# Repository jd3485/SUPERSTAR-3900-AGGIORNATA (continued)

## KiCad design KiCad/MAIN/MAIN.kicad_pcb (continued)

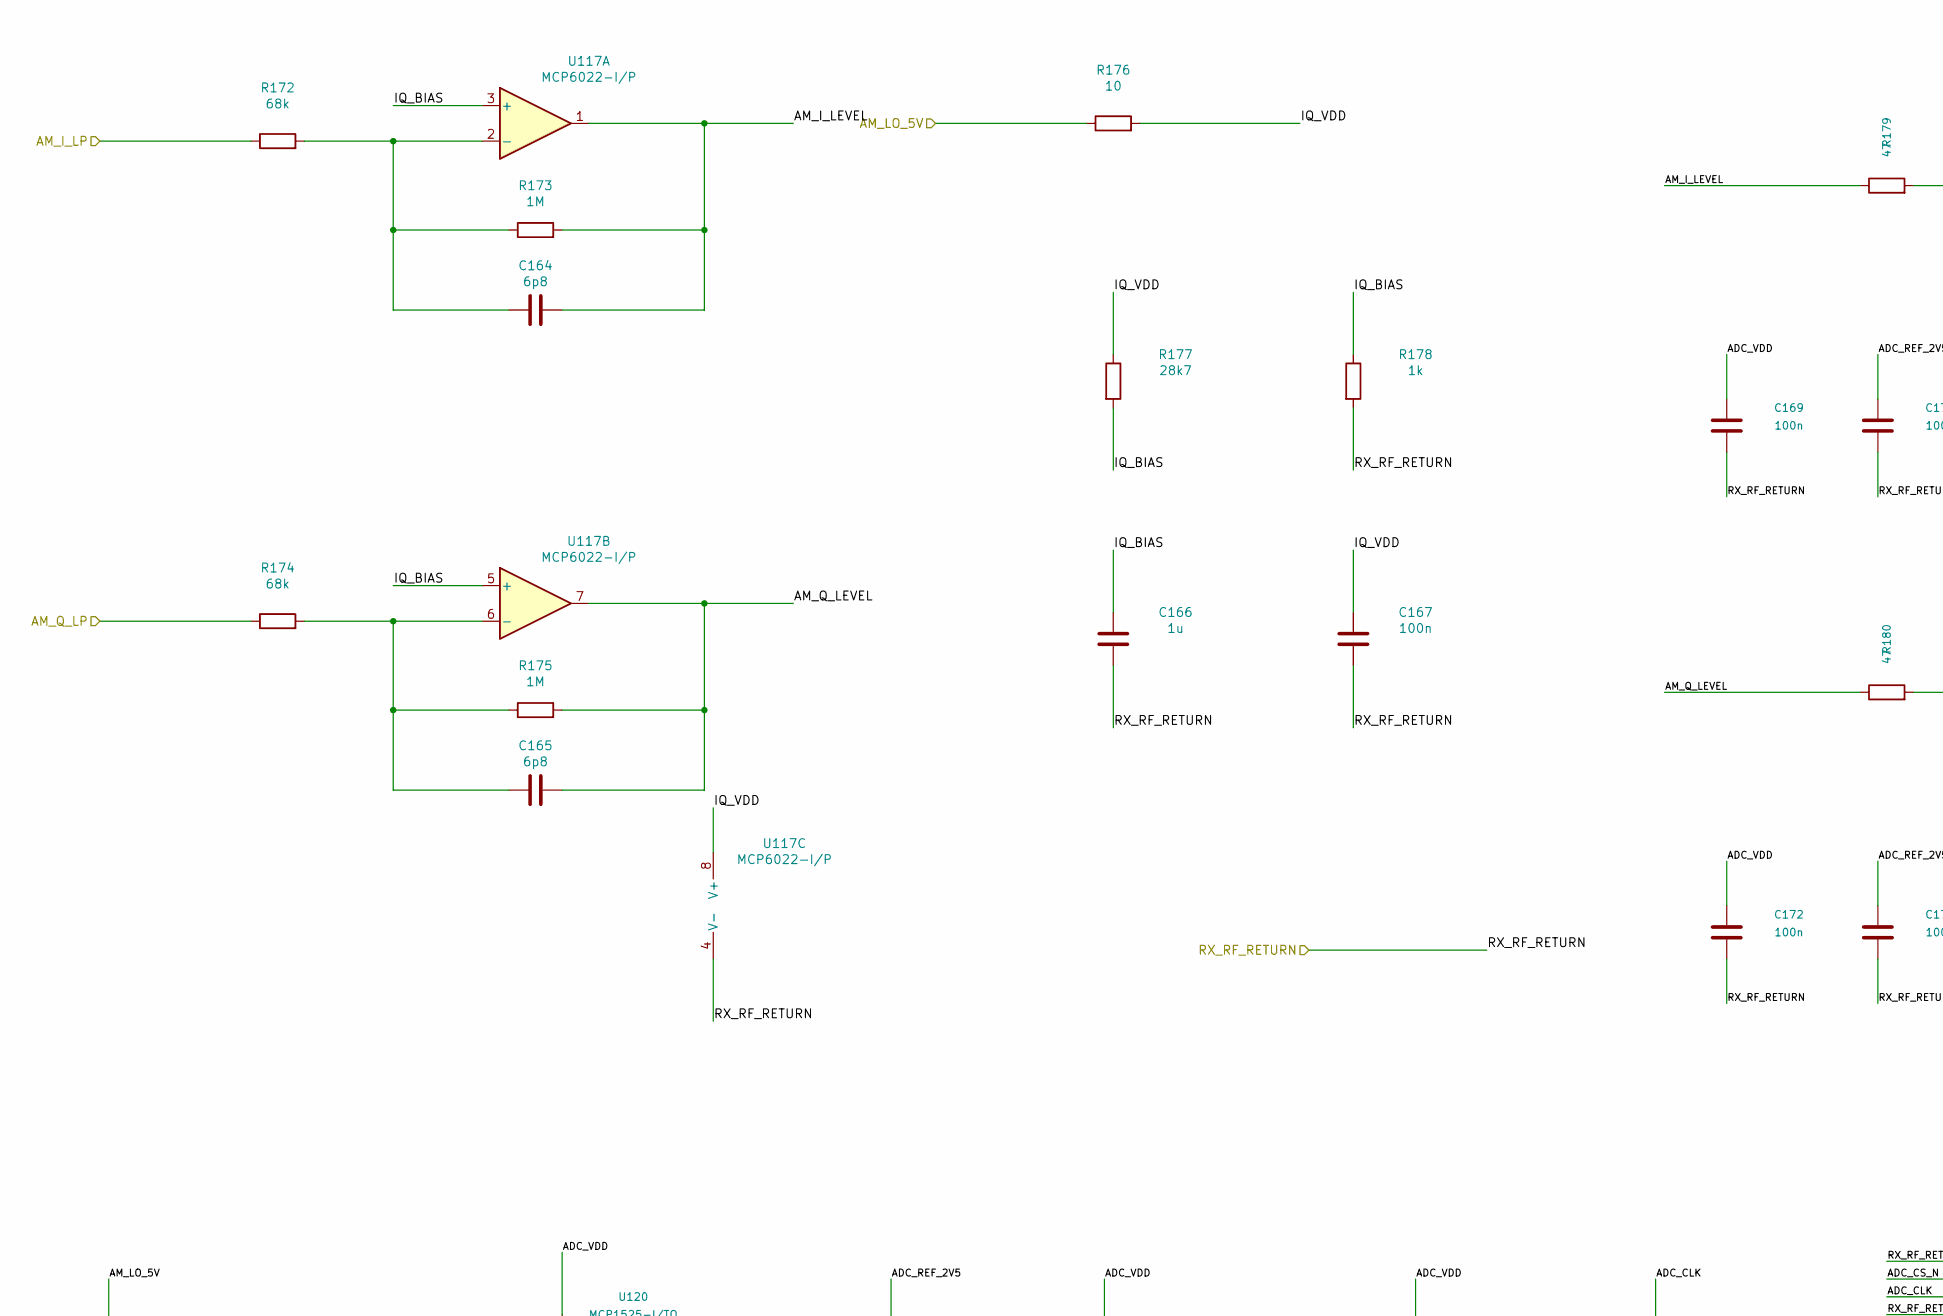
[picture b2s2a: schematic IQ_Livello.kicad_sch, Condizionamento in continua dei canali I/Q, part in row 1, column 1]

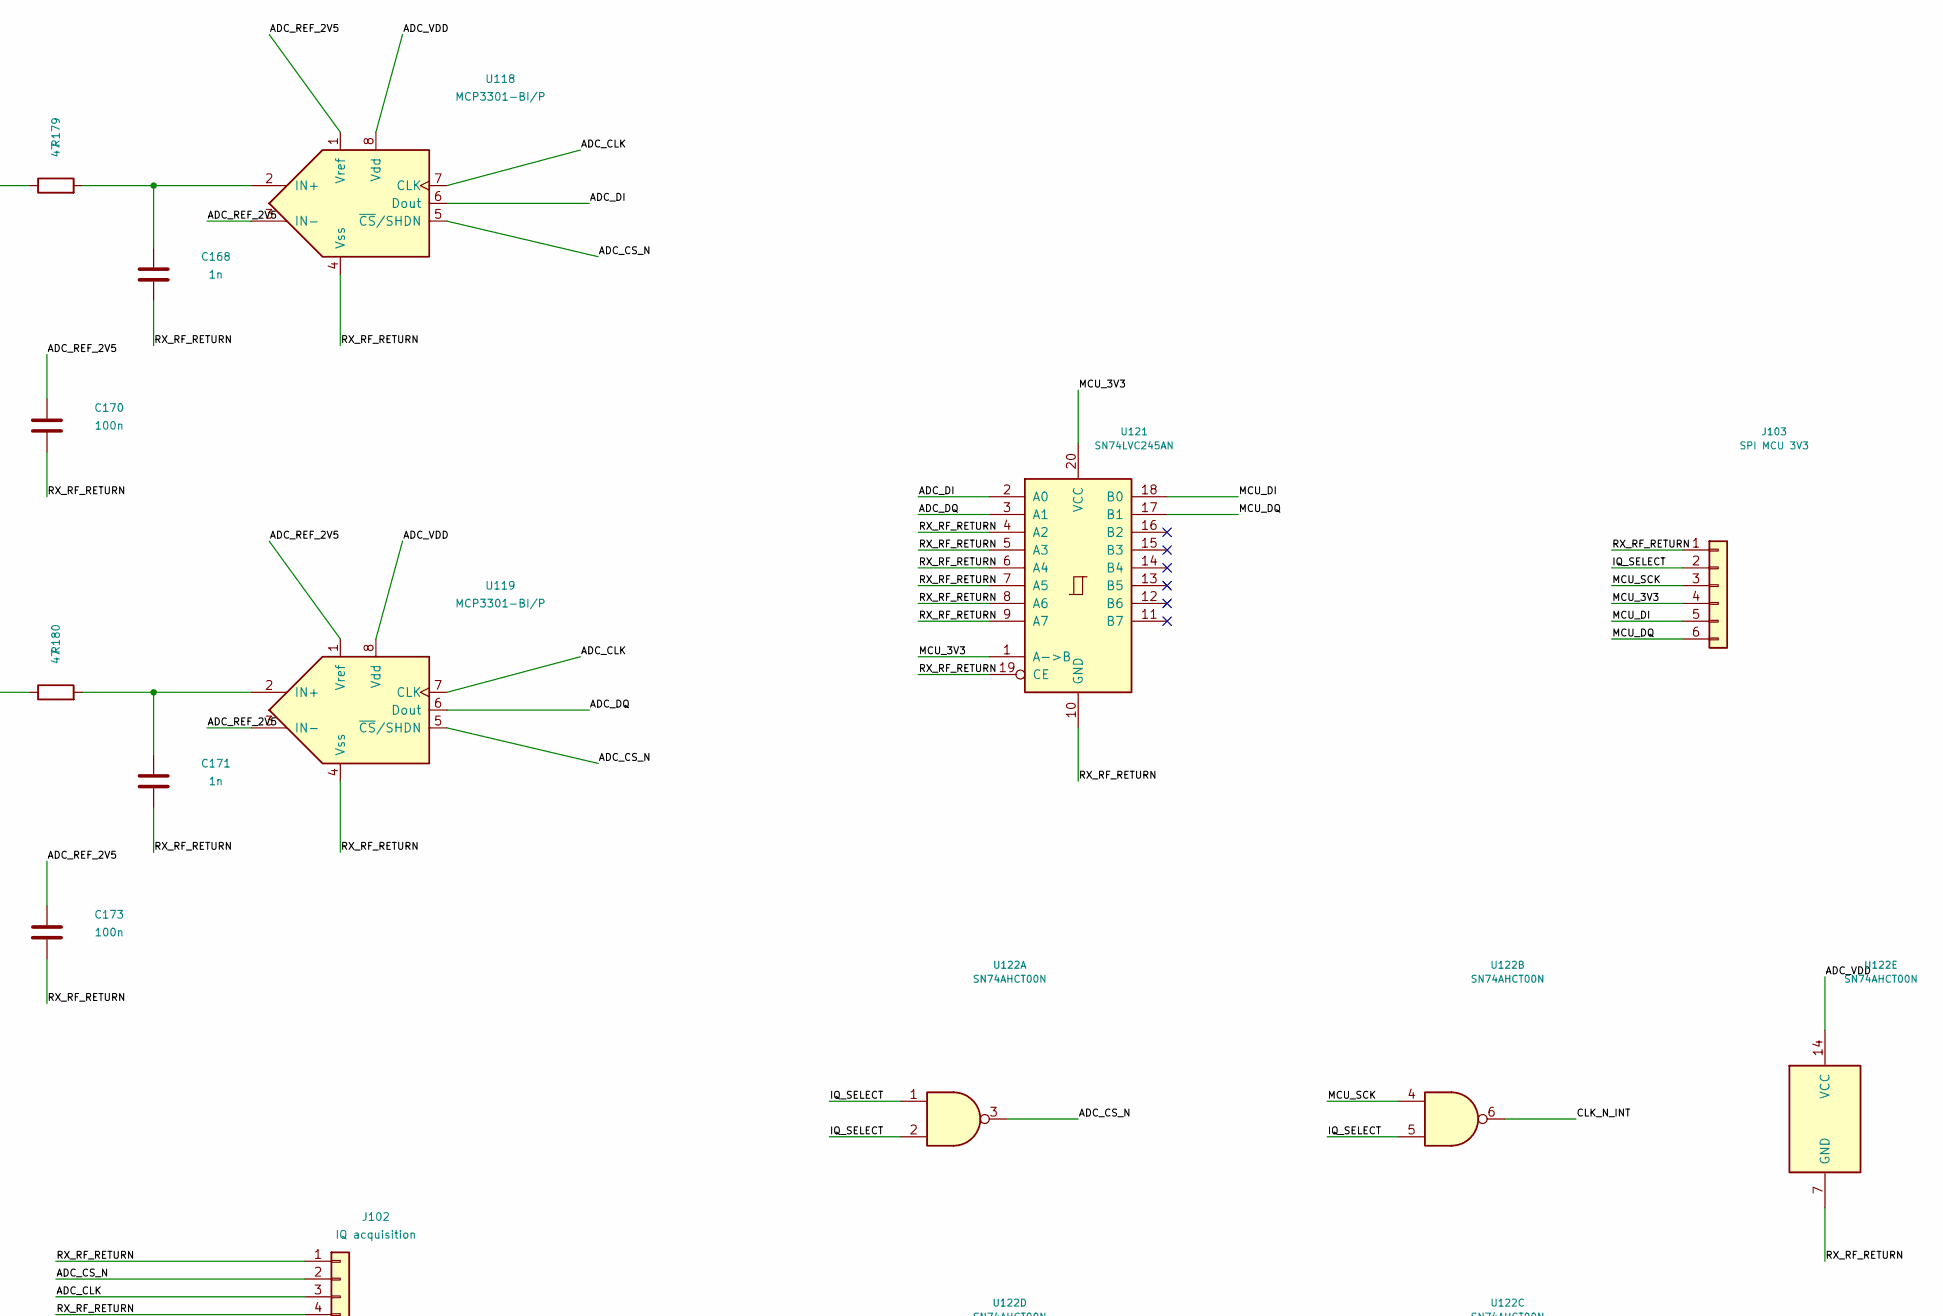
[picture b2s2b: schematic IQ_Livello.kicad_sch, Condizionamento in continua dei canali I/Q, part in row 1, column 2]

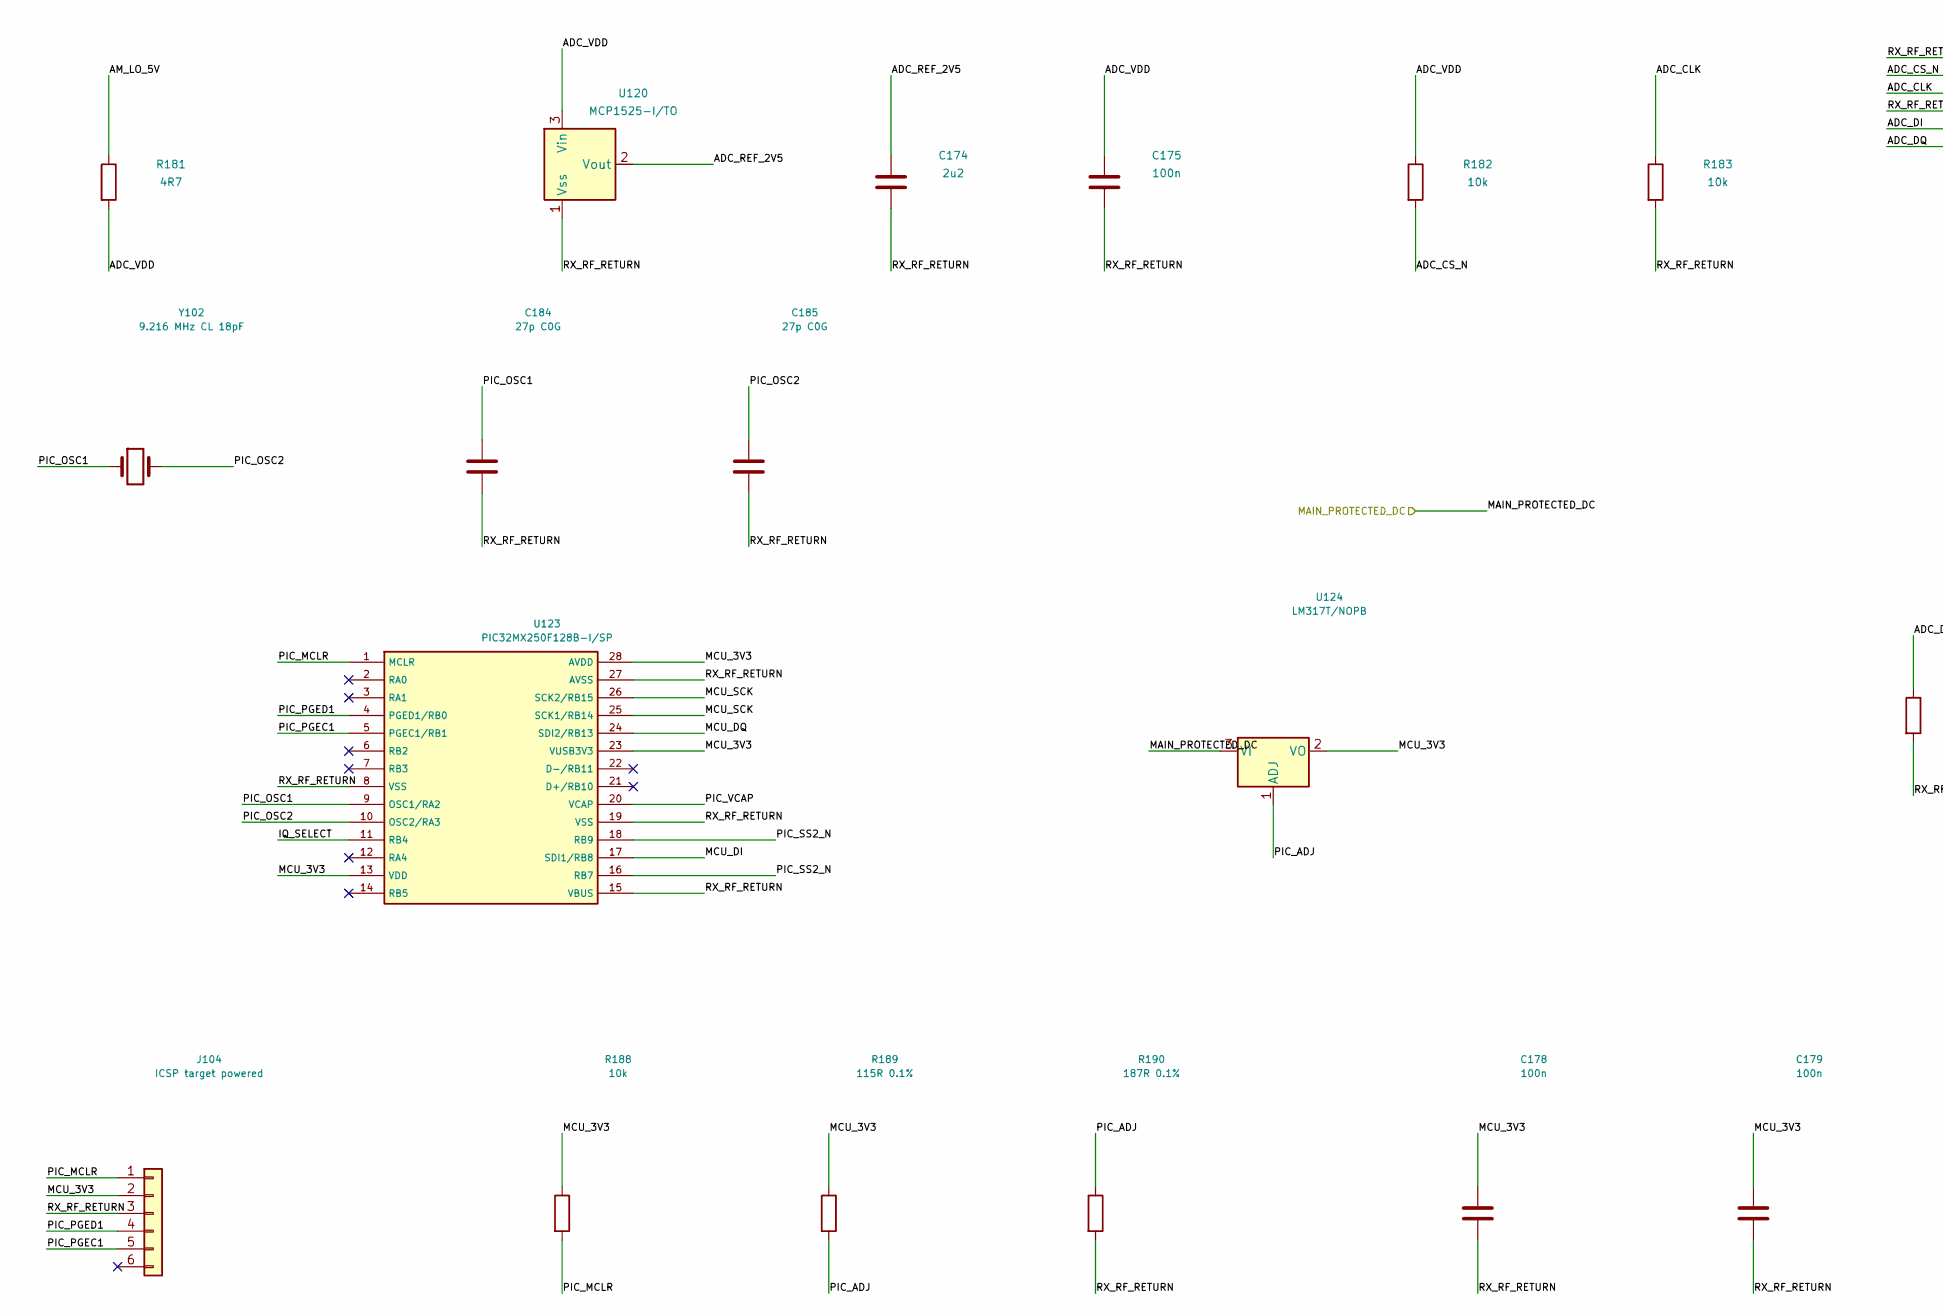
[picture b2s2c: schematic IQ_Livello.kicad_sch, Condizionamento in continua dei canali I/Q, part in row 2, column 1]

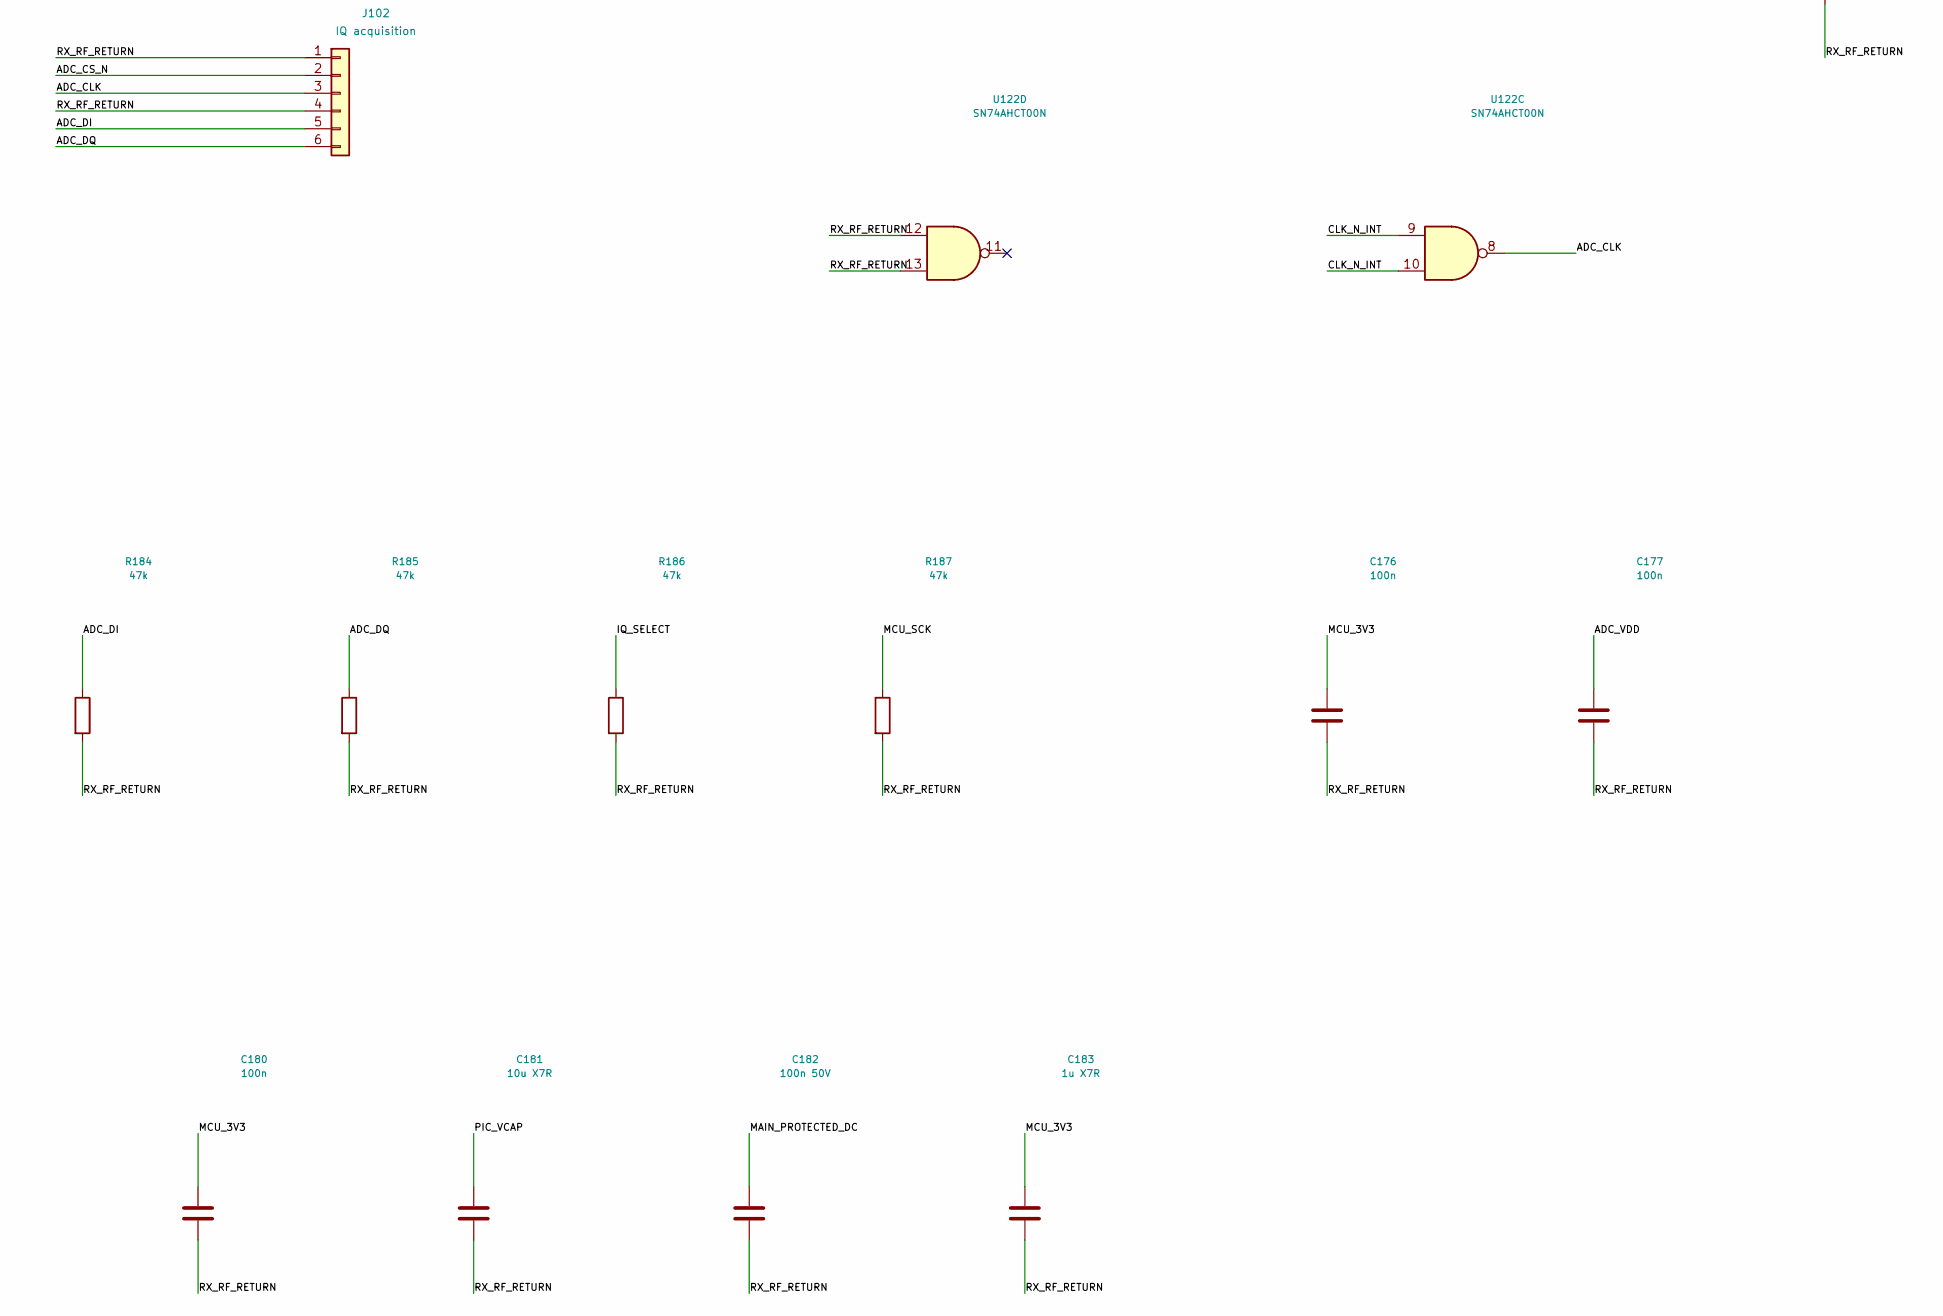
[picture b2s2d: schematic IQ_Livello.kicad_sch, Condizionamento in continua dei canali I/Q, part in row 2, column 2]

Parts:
C164, C165: 6p8; C_Disc_D3.0mm_W1.6mm_P2.50mm
C166: 1u; C_Rect_L7.0mm_W4.5mm_P5.00mm
C167, C169, C170, C172, C173, C175, C176, C177, C178, C179, C180: 100n; C_Rect_L4.0mm_W2.5mm_P2.50mm
C168, C171: 1n; C_Rect_L4.0mm_W2.5mm_P2.50mm
C174: 2u2; C_Rect_L7.0mm_W4.5mm_P5.00mm
C181: 10u X7R; C_Rect_L7.0mm_W4.5mm_P5.00mm
C182: 100n 50V; C_Rect_L4.0mm_W2.5mm_P2.50mm
C183: 1u X7R; C_Rect_L7.0mm_W4.5mm_P5.00mm
C184, C185: 27p C0G; C_Rect_L4.0mm_W2.5mm_P2.50mm
J102: IQ acquisition; PinHeader_1x06_P2.54mm_Vertical
J103: SPI MCU 3V3; PinHeader_1x06_P2.54mm_Vertical
J104: ICSP target powered; PinHeader_1x06_P2.54mm_Vertical
R172, R174: 68k; R_Axial_DIN0207_L6.3mm_D2.5mm_P7.62mm_Horizontal
R173, R175: 1M; R_Axial_DIN0207_L6.3mm_D2.5mm_P7.62mm_Horizontal
R176: 10; R_Axial_DIN0207_L6.3mm_D2.5mm_P7.62mm_Horizontal
R177: 28k7; R_Axial_DIN0207_L6.3mm_D2.5mm_P7.62mm_Horizontal
R178: 1k; R_Axial_DIN0207_L6.3mm_D2.5mm_P7.62mm_Horizontal
R179, R180: 47; R_Axial_DIN0207_L6.3mm_D2.5mm_P7.62mm_Horizontal
R181: 4R7; R_Axial_DIN0207_L6.3mm_D2.5mm_P7.62mm_Horizontal
R182, R183, R188: 10k; R_Axial_DIN0207_L6.3mm_D2.5mm_P7.62mm_Horizontal
R184, R185, R186, R187: 47k; R_Axial_DIN0207_L6.3mm_D2.5mm_P7.62mm_Horizontal
R189: 115R 0.1%; R_Axial_DIN0207_L6.3mm_D2.5mm_P7.62mm_Horizontal
R190: 187R 0.1%; R_Axial_DIN0207_L6.3mm_D2.5mm_P7.62mm_Horizontal
U117: MCP6022-I/P; DIP-8_W7.62mm
U118, U119: MCP3301-BI/P; DIP-8_W7.62mm
U120: MCP1525-I/TO; TO-92_Inline
U121: SN74LVC245AN; DIP-20_W7.62mm
U122: SN74AHCT00N; DIP-14_W7.62mm
U123: PIC32MX250F128B-I/SP; DIP-28_W7.62mm
U124: LM317T/NOPB; TO-220-3_Vertical
Y102: 9.216 MHz CL 18pF; Crystal_HC49-U_Vertical

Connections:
/AM_I_LP: R172.1; also elsewhere on the board
/AM_LO_5V: R176.1, R181.1; also elsewhere on the board
/AM_Q_LP: R174.1; also elsewhere on the board
/Condizionamento IQ/ADC_CLK: J102.3, R183.1, U118.7 (CLK), U119.7 (CLK), U122.8
/Condizionamento IQ/ADC_CS_N: J102.2, R182.2, U118.5 (~CS/SHDN), U119.5 (~CS/SHDN), U122.3
/Condizionamento IQ/ADC_DI: J102.5, R184.1, U118.6 (Dout), U121.2 (A0)
/Condizionamento IQ/ADC_DQ: J102.6, R185.1, U119.6 (Dout), U121.3 (A1)
/Condizionamento IQ/ADC_REF_2V5: C170.1, C173.1, C174.1, U118.1 (Vref), U118.3 (IN-), U119.1 (Vref), U119.3 (IN-), U120.2 (Vout)
/Condizionamento IQ/ADC_VDD: C169.1, C172.1, C175.1, C177.1, R181.2, R182.1, U118.8 (Vdd), U119.8 (Vdd), U120.3 (Vin), U122.14 (VCC)
/Condizionamento IQ/AM_I_LEVEL: C164.2, R173.2, R179.1, U117.1
/Condizionamento IQ/AM_Q_LEVEL: C165.2, R175.2, R180.1, U117.7
/Condizionamento IQ/CLK_N_INT: U122.6, U122.9, U122.10
/Condizionamento IQ/IQ_BIAS: C166.1, R177.2, R178.1, U117.3 (+), U117.5 (+)
/Condizionamento IQ/IQ_SELECT: J103.2, R186.1, U122.1, U122.2, U122.5, U123.11 (RB4)
/Condizionamento IQ/IQ_VDD: C167.1, R176.2, R177.1, U117.8 (V+)
/Condizionamento IQ/MCU_3V3: C176.1, C178.1, C179.1, C180.1, C183.1, J103.4, J104.2, R188.1, R189.1, U121.1 (A->B), U121.20 (VCC), U123.13 (VDD), U123.23 (VUSB3V3), U123.28 (AVDD), U124.2 (VO)
/Condizionamento IQ/MCU_DI: J103.5, U121.18 (B0), U123.17 (SDI1/RB8)
/Condizionamento IQ/MCU_DQ: J103.6, U121.17 (B1), U123.24 (SDI2/RB13)
/Condizionamento IQ/MCU_SCK: J103.3, R187.1, U122.4, U123.25 (SCK1/RB14), U123.26 (SCK2/RB15)
/Condizionamento IQ/PIC_ADJ: R189.2, R190.1, U124.1 (ADJ)
/Condizionamento IQ/PIC_MCLR: J104.1, R188.2, U123.1 (MCLR)
/Condizionamento IQ/PIC_OSC1: C184.1, U123.9 (OSC1/RA2), Y102.1
/Condizionamento IQ/PIC_OSC2: C185.1, U123.10 (OSC2/RA3), Y102.2
/Condizionamento IQ/PIC_PGEC1: J104.5, U123.5 (PGEC1/RB1)
/Condizionamento IQ/PIC_PGED1: J104.4, U123.4 (PGED1/RB0)
/Condizionamento IQ/PIC_SS2_N: U123.16 (RB7), U123.18 (RB9)
/Condizionamento IQ/PIC_VCAP: C181.1, U123.20 (VCAP)
/MAIN_PROTECTED_DC: C182.1, U124.3 (VI); also elsewhere on the board
/RX_RF_RETURN: C166.2, C167.2, C168.2, C169.2, C170.2, C171.2, C172.2, C173.2, C174.2, C175.2, C176.2, C177.2, C178.2, C179.2, C180.2, C181.2, C182.2, C183.2, C184.2, C185.2, J102.1, J102.4, J103.1, J104.3, R178.2, R183.2, R184.2, R185.2, R186.2, R187.2, R190.2, U117.4 (V-), U118.4 (Vss), U119.4 (Vss), U120.1 (Vss), U121.4 (A2), U121.5 (A3), U121.6 (A4), U121.7 (A5), U121.8 (A6), U121.9 (A7), U121.10 (GND), U121.19 (CE), U122.7 (GND), U122.12, U122.13, U123.8 (VSS), U123.15 (VBUS), U123.19 (VSS), U123.27 (AVSS); also elsewhere on the board
unnamed: C164.1, R172.2, R173.1, U117.2 (-)
unnamed: C165.1, R174.2, R175.1, U117.6 (-)
unnamed: C168.1, R179.2, U118.2 (IN+)
unnamed: C171.1, R180.2, U119.2 (IN+)

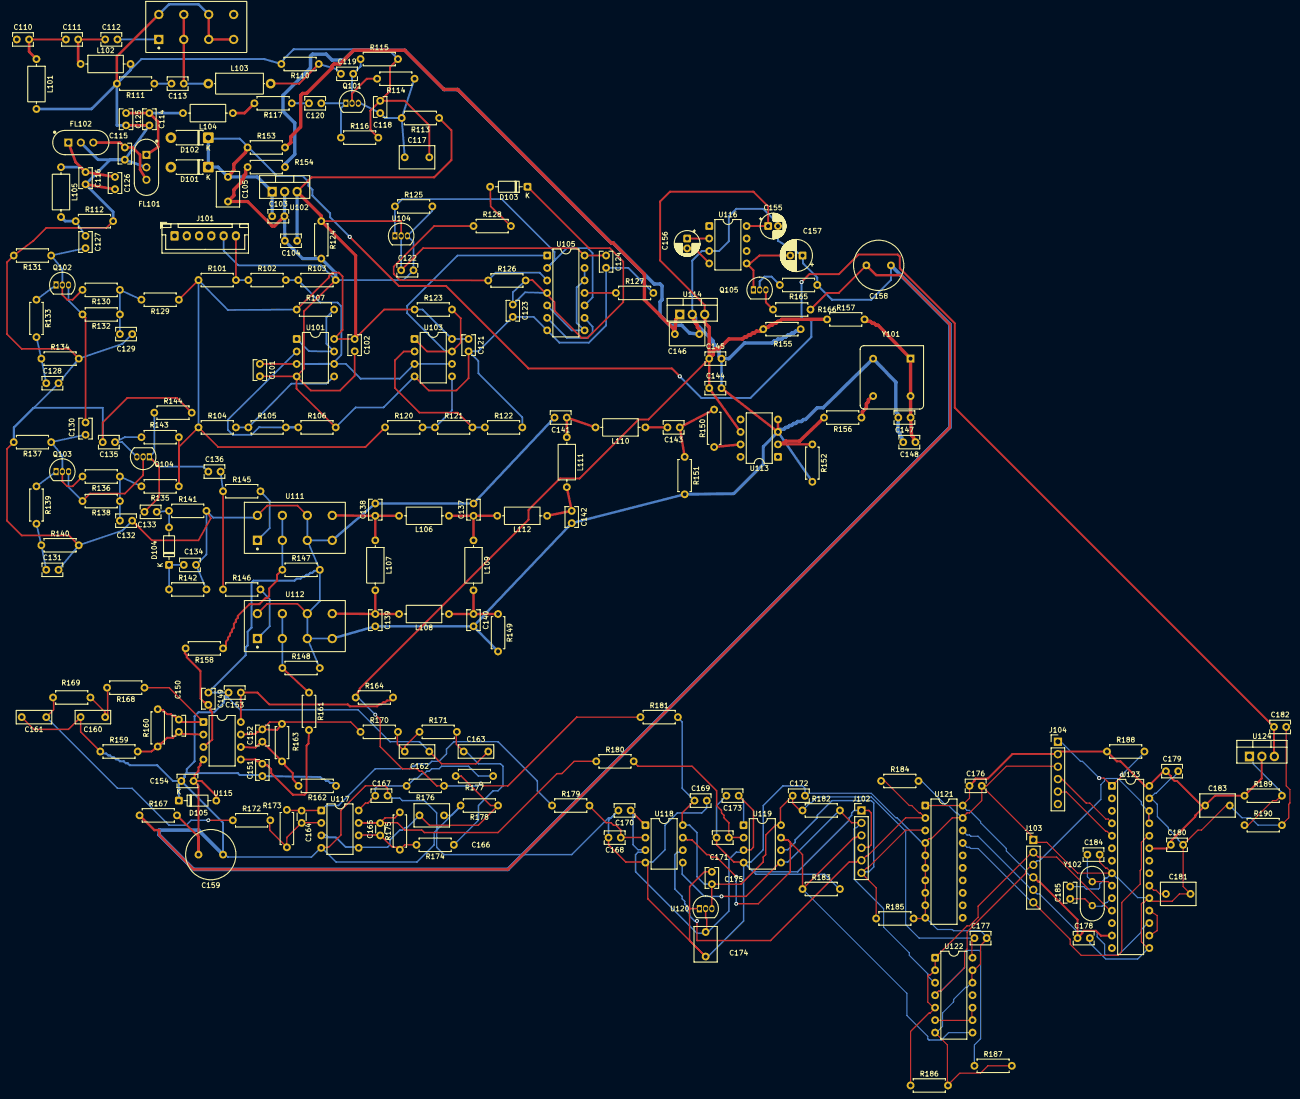
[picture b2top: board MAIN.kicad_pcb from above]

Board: 2 copper layers, 217 parts (0 on the bottom side), 113 nets.
